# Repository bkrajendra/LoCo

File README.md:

# LoCo - A LoRa-concentrator

An Opensource LoRa Concentrator/Gateway using SX1301/SX1308 and SX1255/SX1257 For RRI and RPI Zero.

This project is heavyly inspired and adapted from @will127534 works he has done for his contribution at https://github.com/will127534/LoRa-concentrator.

We just want to take this project ahead and updating it with most commonly avialibility of componenets.

The first step is to port the schematic to KiCad to make the process of devlopment easier as an opensource project.

<!-- Copy-paste in your Readme.md file -->
## Contributors

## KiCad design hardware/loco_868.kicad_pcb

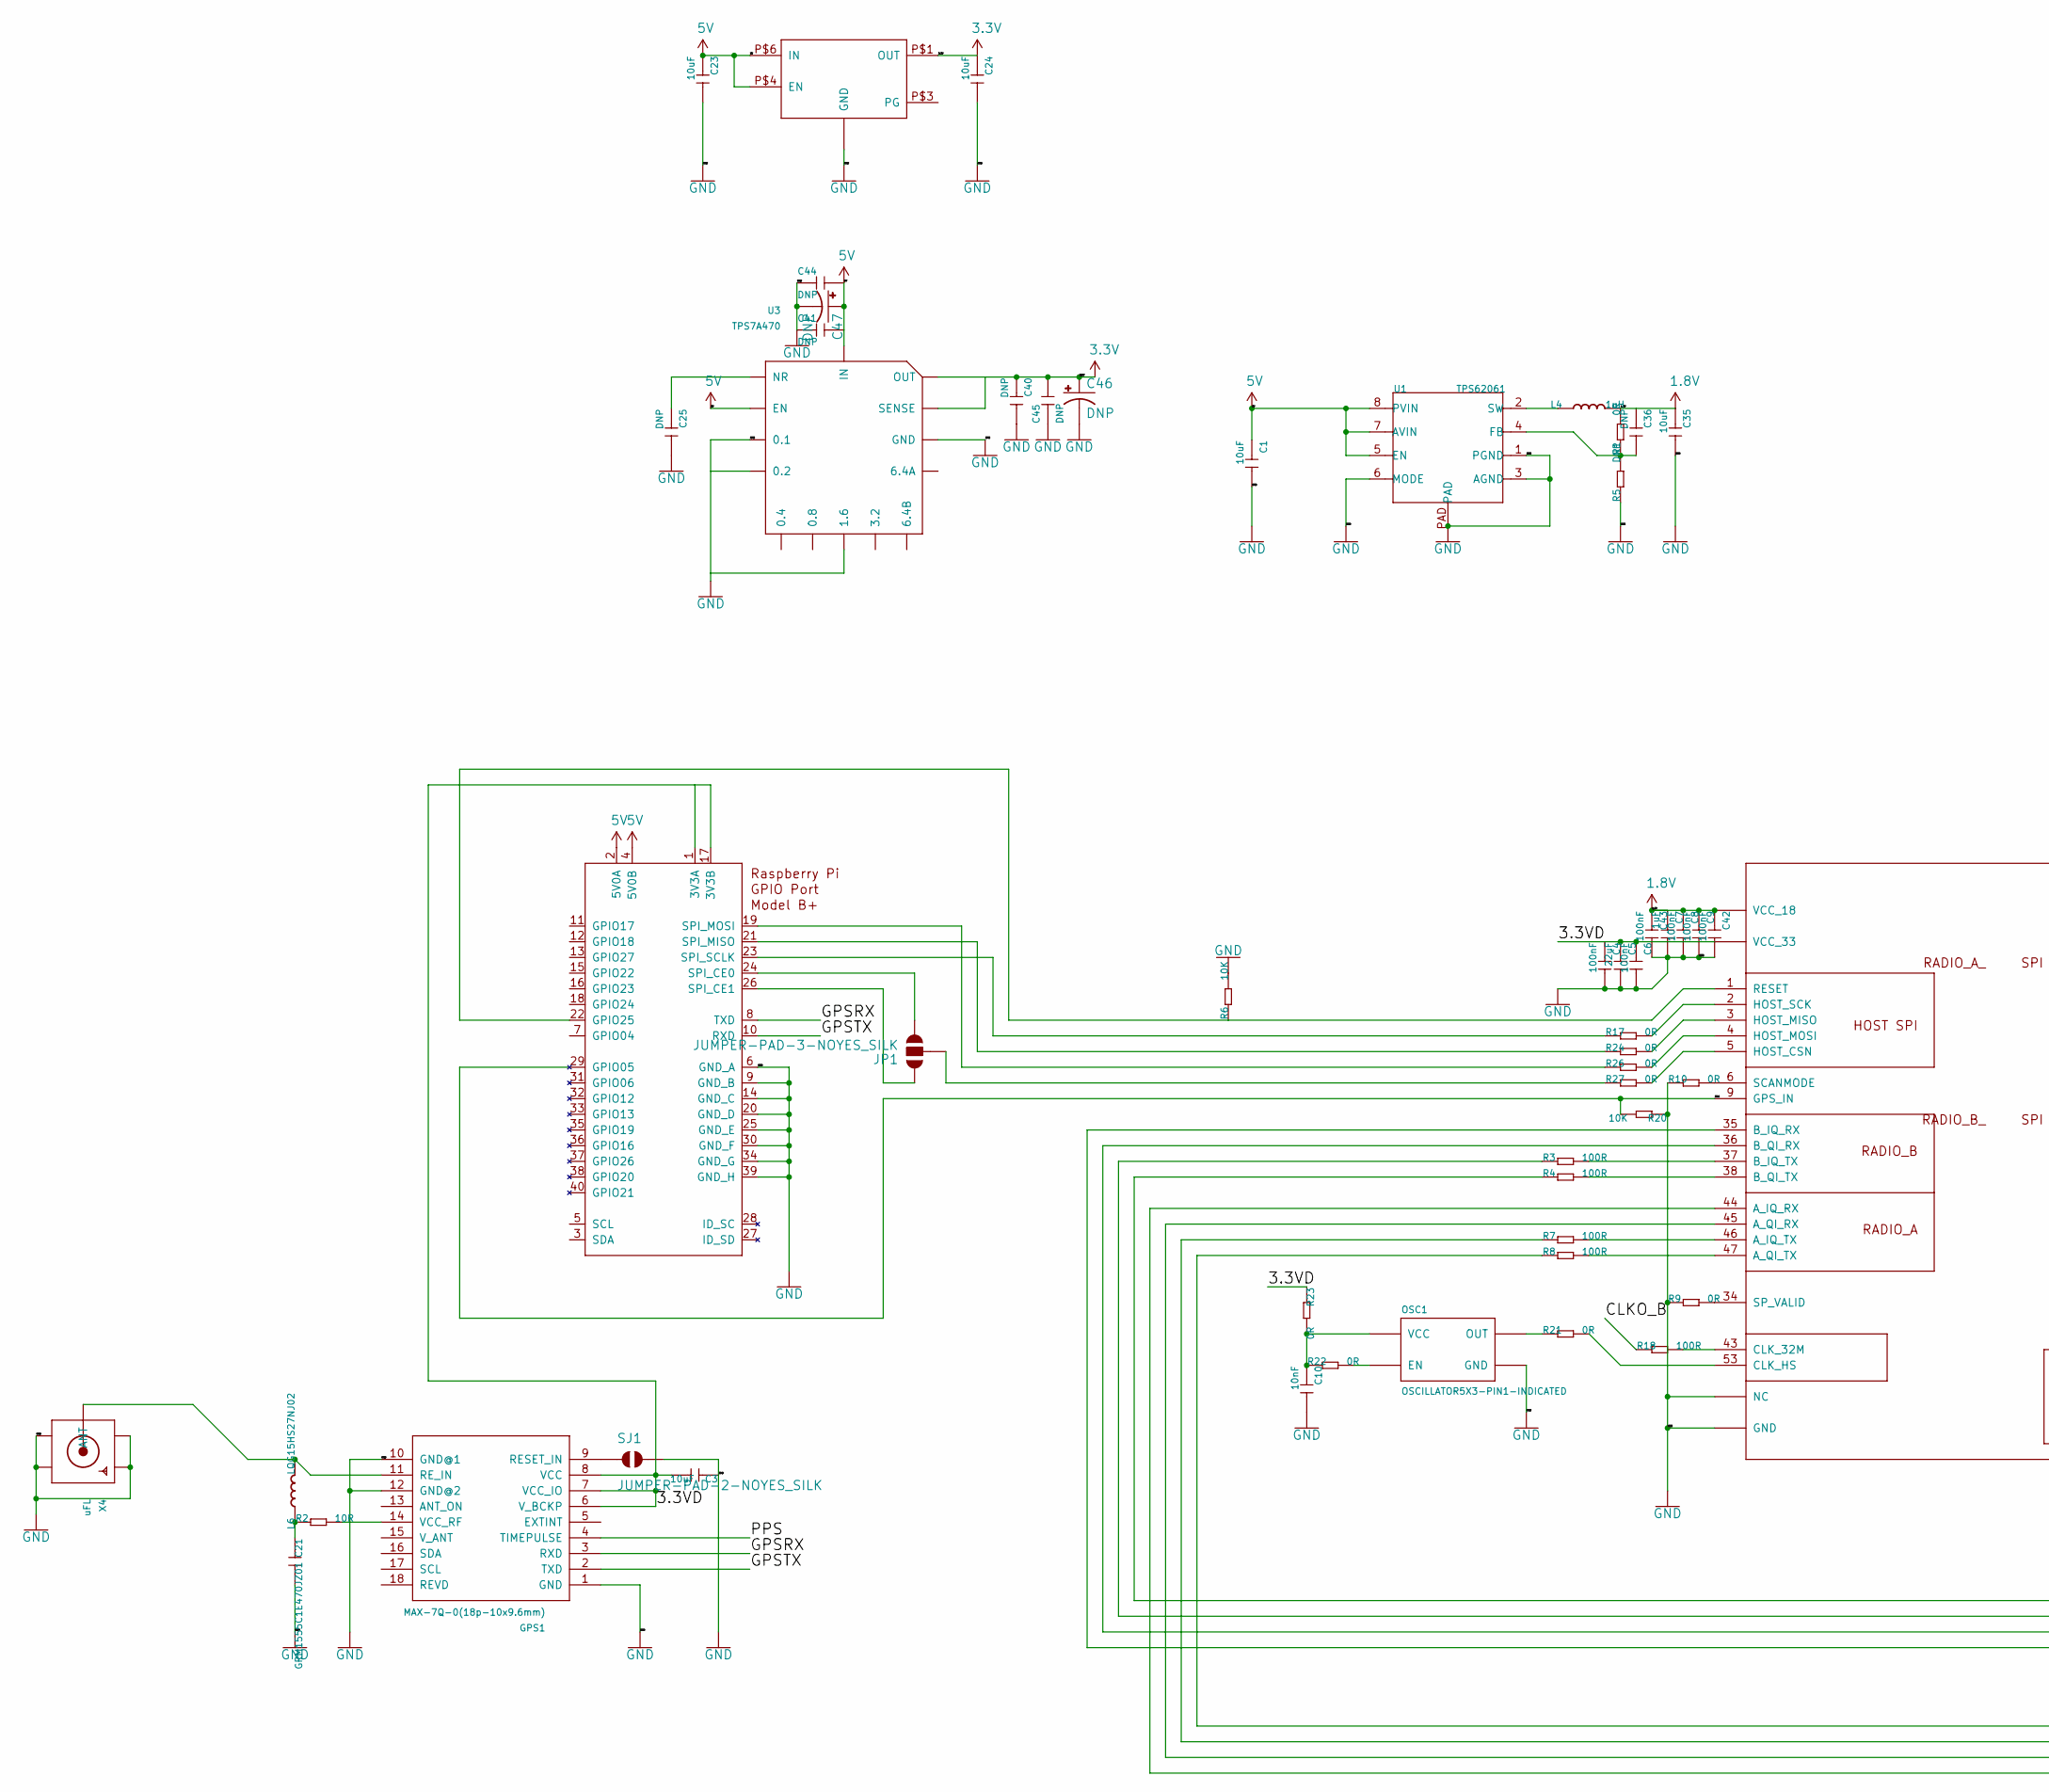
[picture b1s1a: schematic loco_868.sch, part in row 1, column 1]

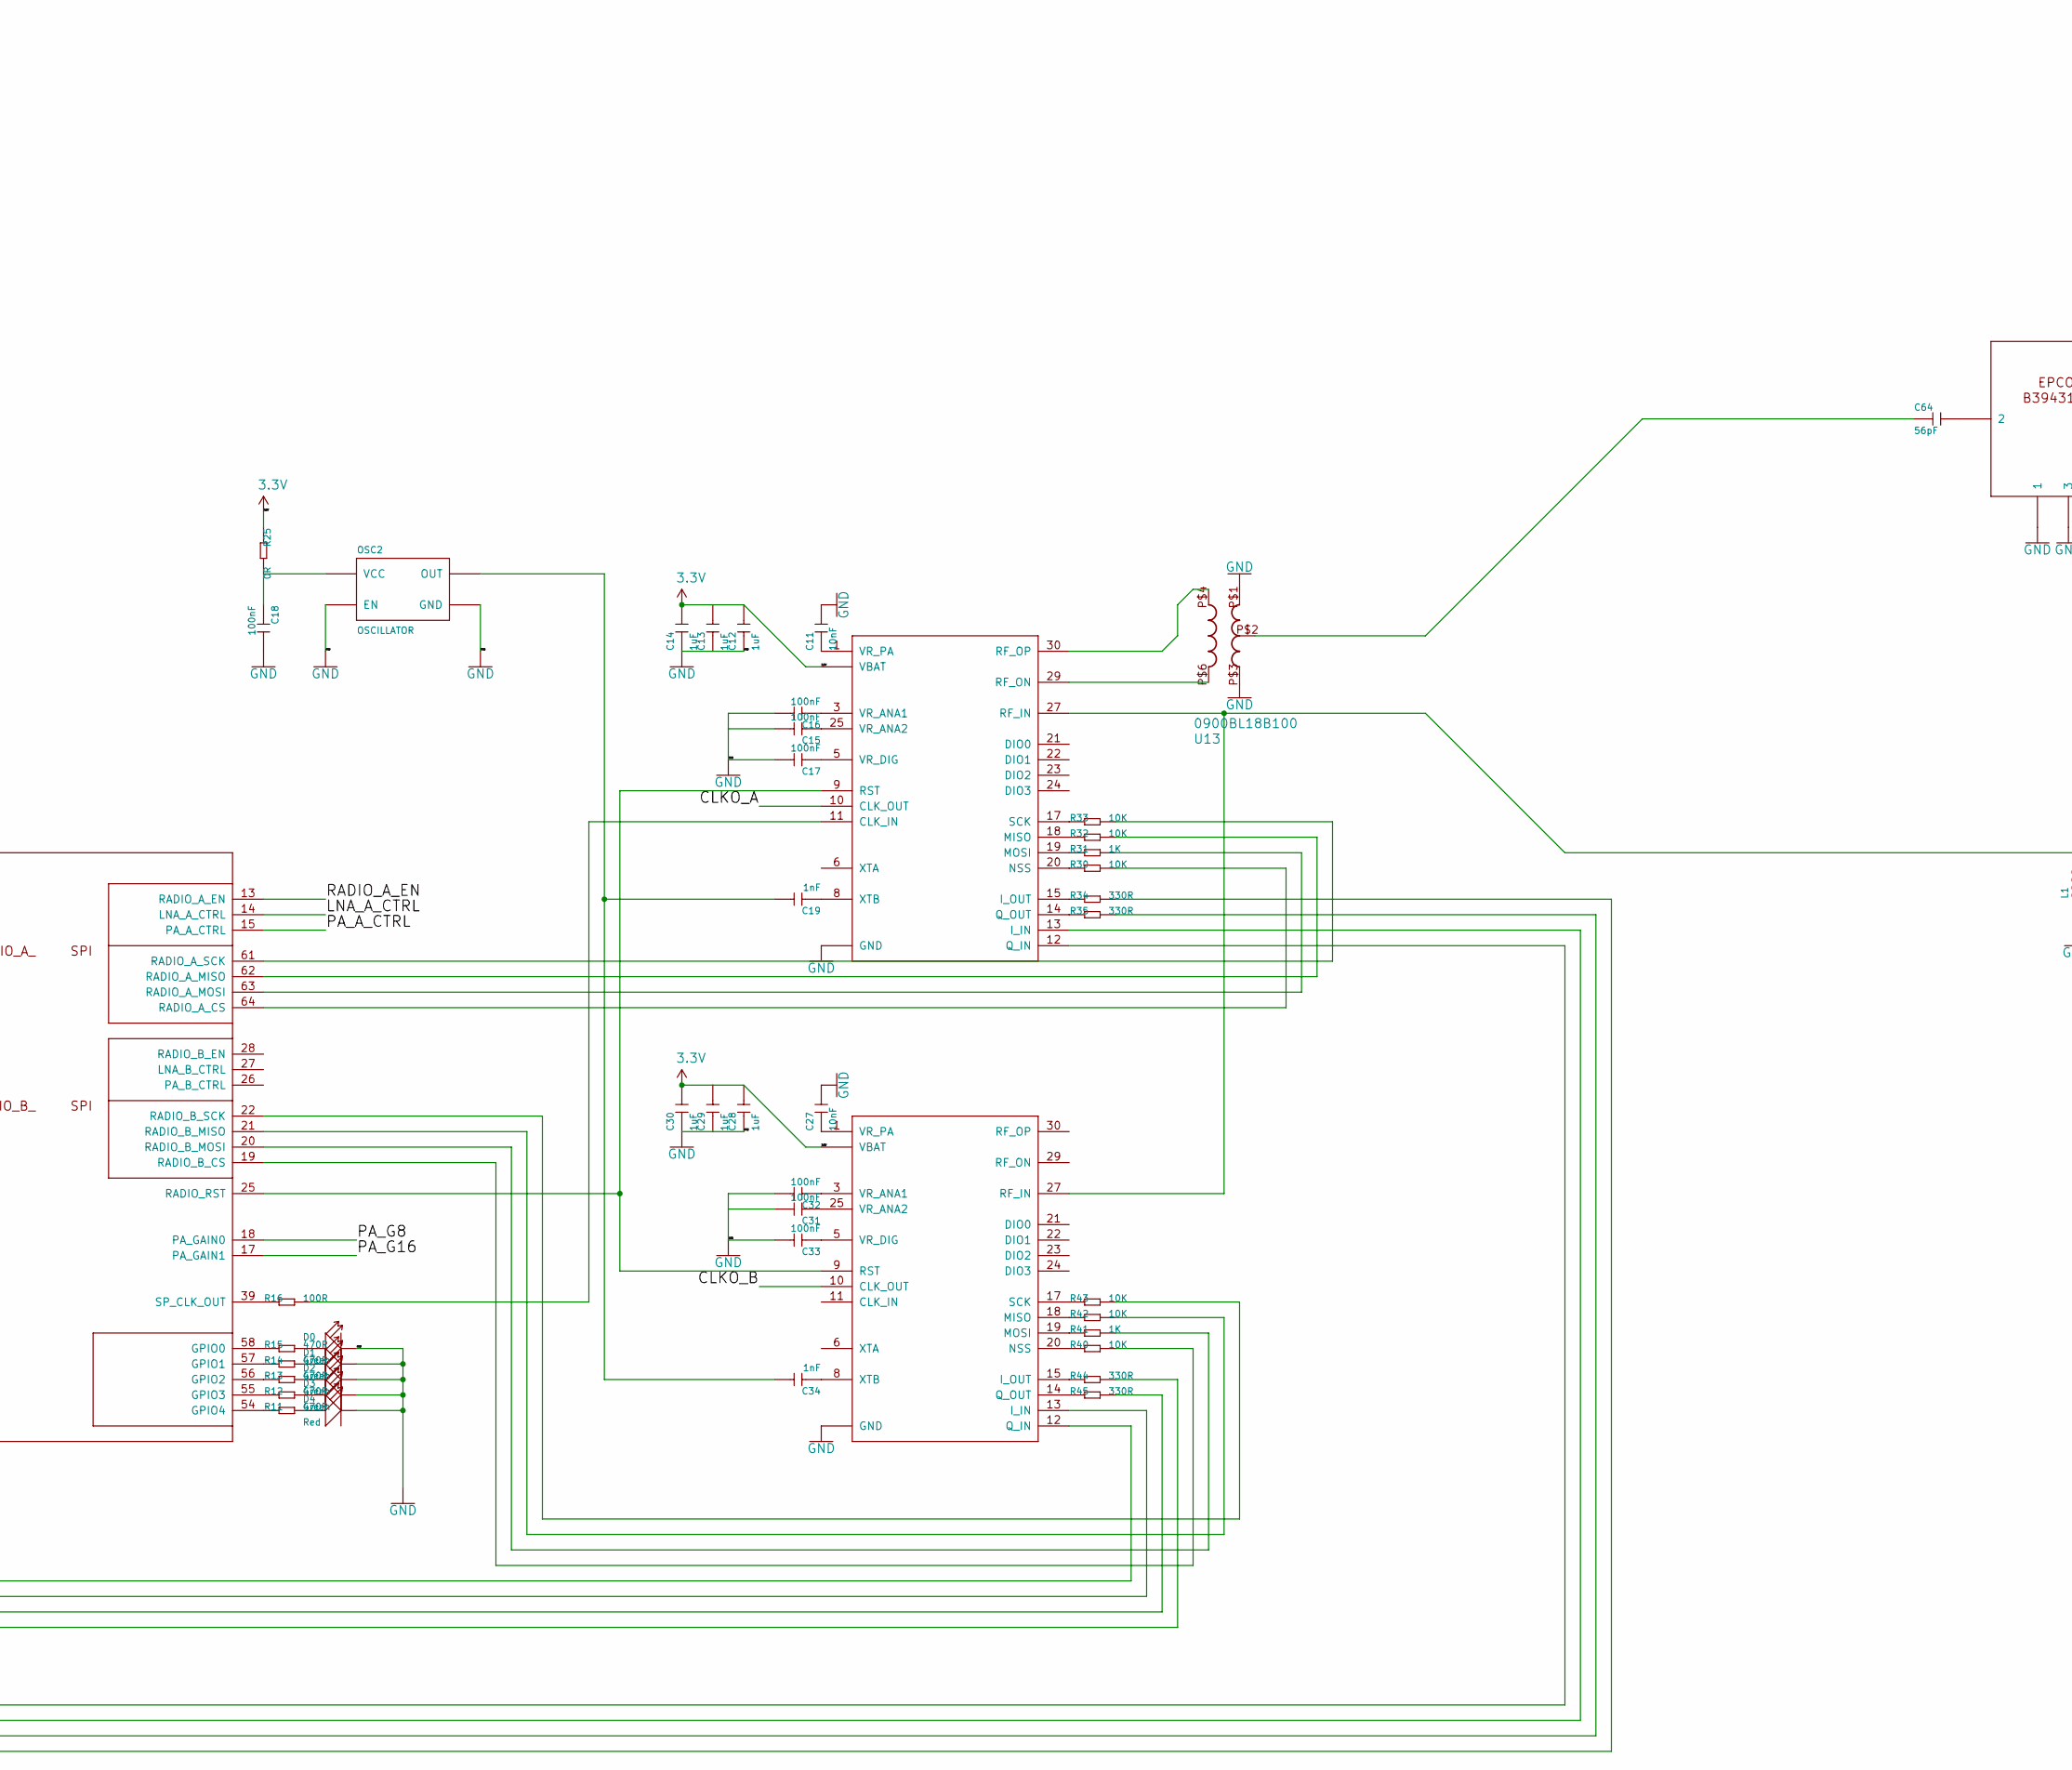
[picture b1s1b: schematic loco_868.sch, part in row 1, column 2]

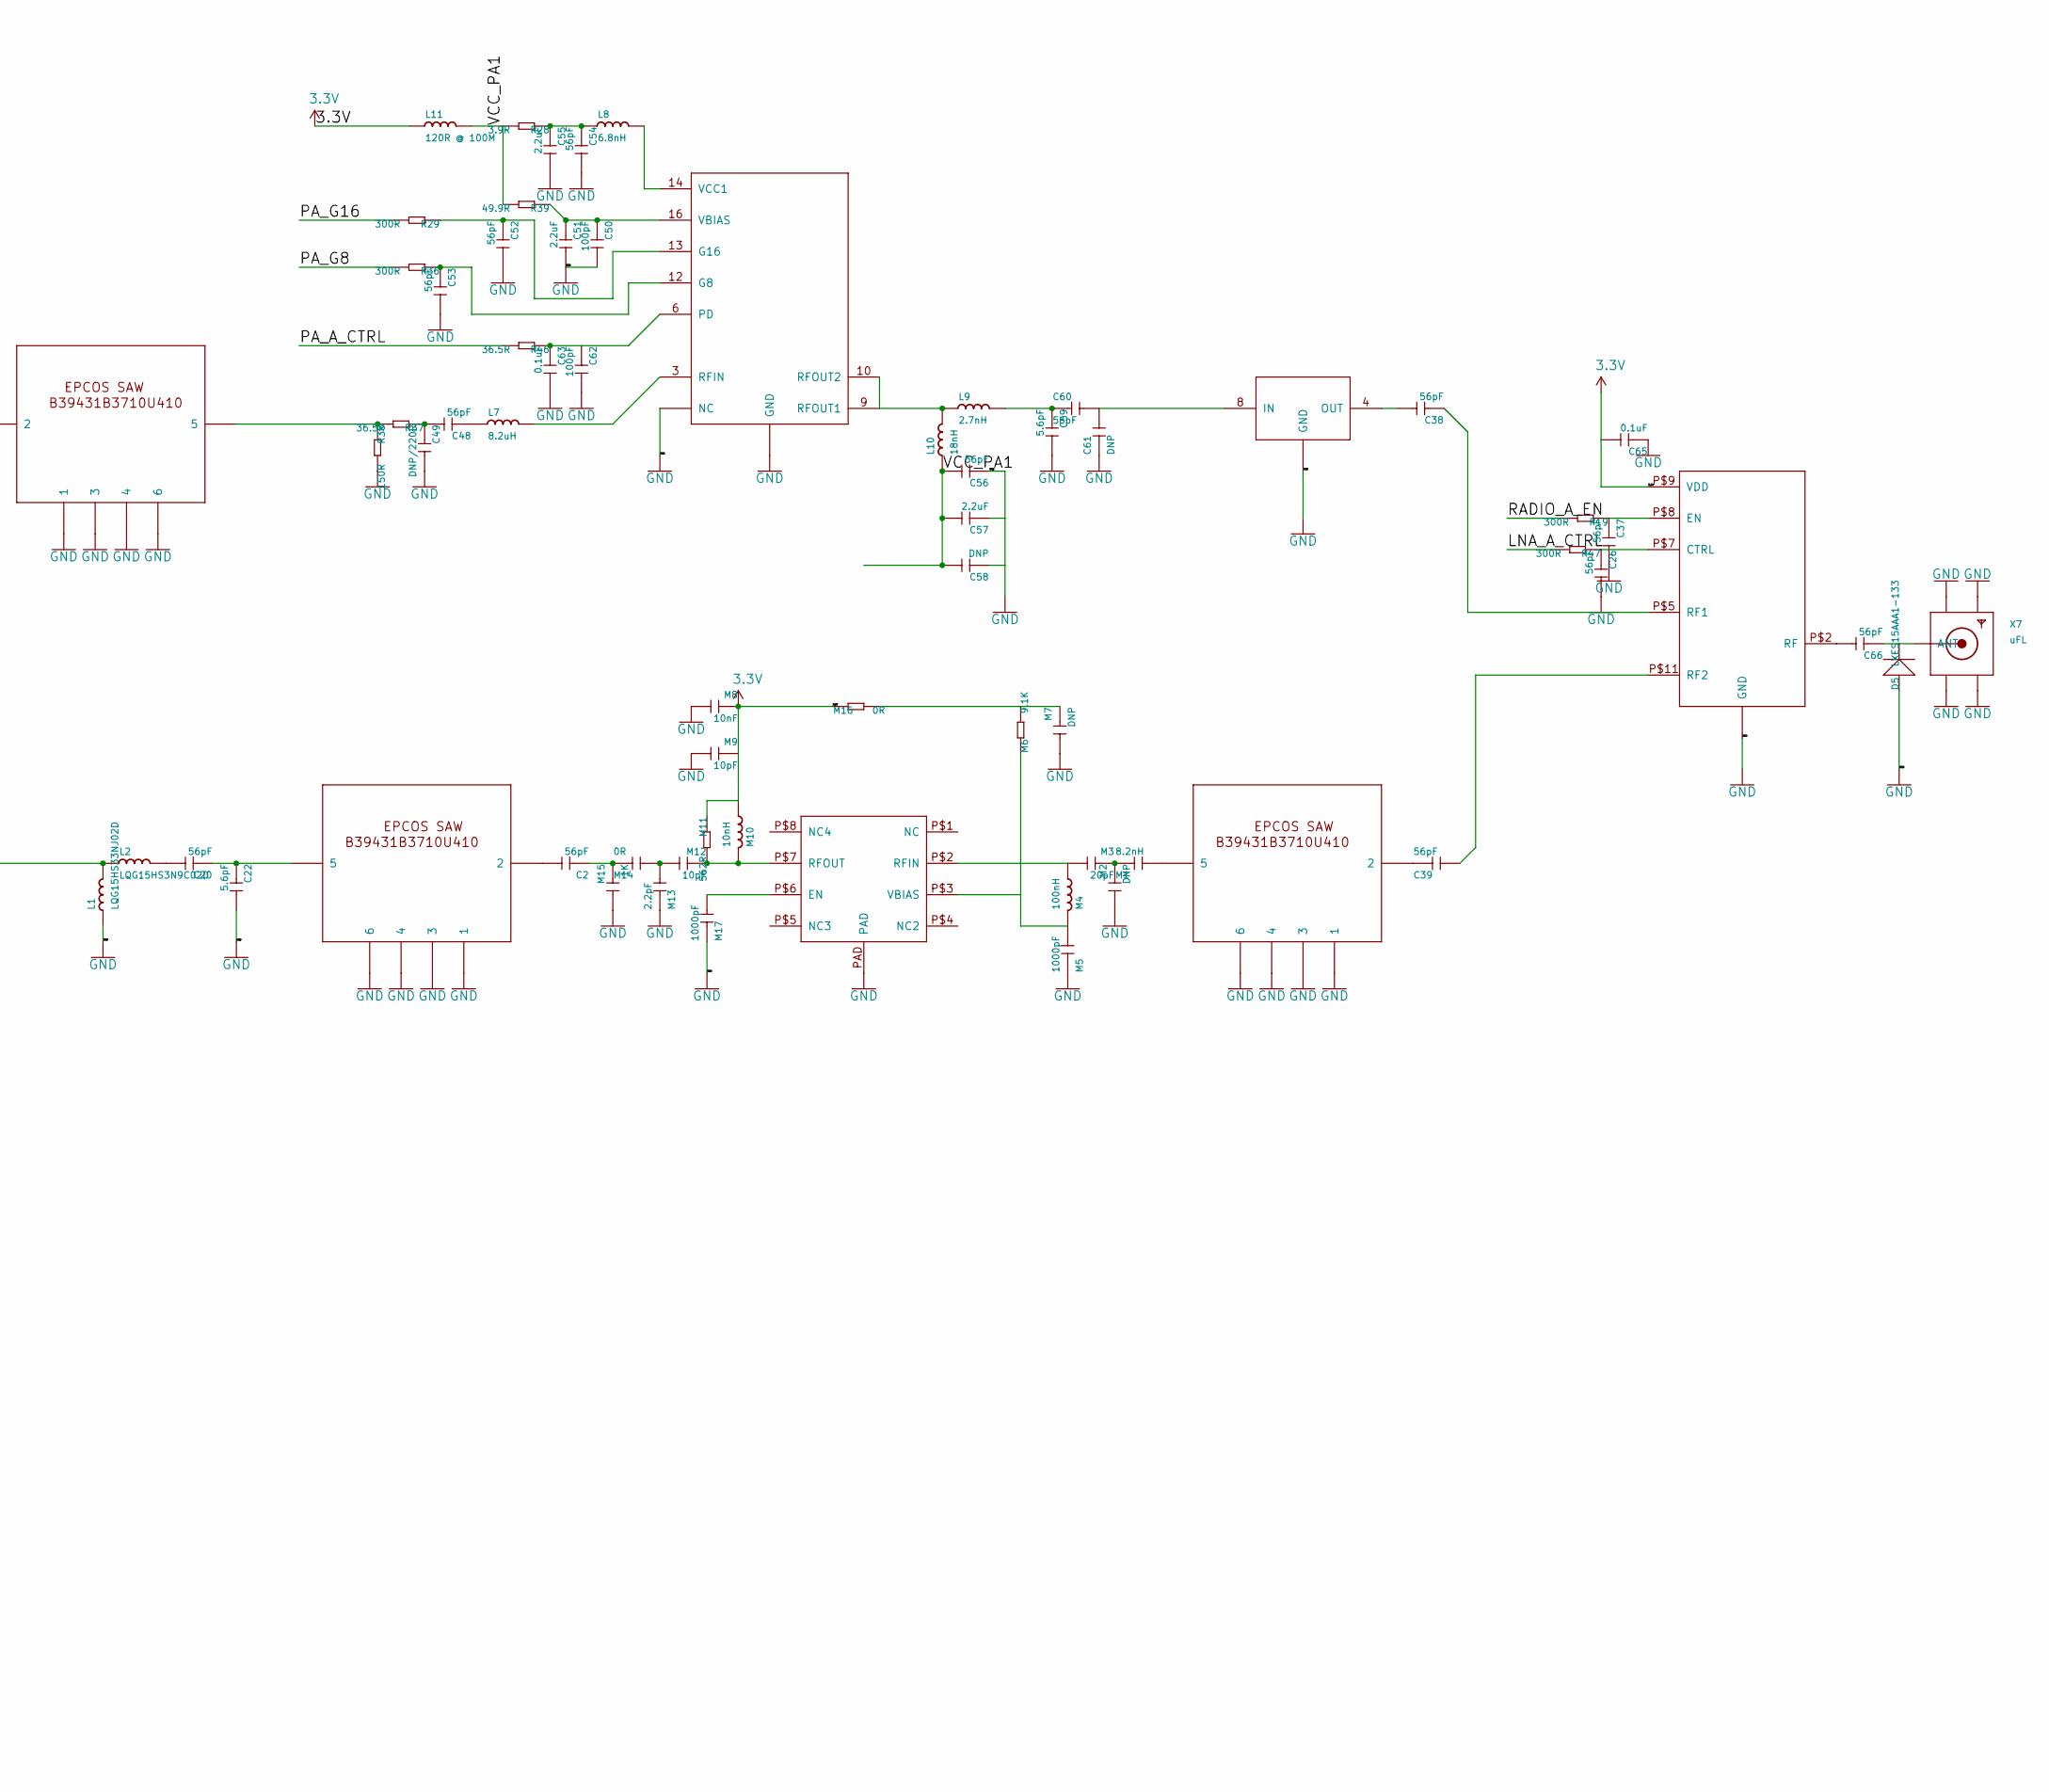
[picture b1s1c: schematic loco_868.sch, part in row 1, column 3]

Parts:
C1, C23, C24, C35: 10uF; C0603@1
C2, C20, C26, C37, C38, C39, C48, C52, C53, C54, C56, C60, C64, C66: 56pF; C0402@1
C3: 10uF; C0603
C4, C6, C8, C9, C15, C16, C17, C18, C31, C32, C33, C42, C43: 100nF; C0402@1
C5: 22uF; C0402@1
C7, C12, C13, C14, C28, C29, C30: 1uF; C0402@1
C10, C11, C27: 10nF; C0402@1
C19, C34: 1nF; C0402@1
C21: GRM1555C1E470JZ01; C0402
C22, C59: 5.6pF; C0402@1
C25, C36, C40, C41, C58, C61: DNP; C0402@1
C44, C45: DNP; C0805@1
C46, C47: DNP; EIA3216
C49: DNP/220R; C0402@1
C50, C62: 100pF; C0402@1
C51, C55, C57: 2.2uF; C0402@1
C63, C65: 0.1uF; C0402@1
D0, D1, D2, D3: Green; LED-0603
D4: Red; LED-0603
D5: LXES15AAA1-133; C0402
GPS1: MAX-7Q-0(18p-10x9.6mm); GPS18P-SMD-1.1-10X9.6MM
JP1: JUMPER-PAD-3-NOYES_SILK; PAD-JUMPER-3-NO_YES_SILK
L1: LQG15HS33NJ02D; L0402@1
L2: LQG15HS3N9C02D; L0402@1
L4: 1uH; 1616BZ
L6: LQG15HS27NJ02; L0402
L7: 8.2uH; L0402@1
L8: 6.8nH; L0402@1
L9: 2.7nH; L0402@1
L10: 18nH; L0402@1
L11: 120R @ 100M; L0402@1
M1: 8.2nH; C0402@1
M2, M7: DNP; C0402@1
M3: 20pF; C0402@1
M4: 100nH; L0402@1
M5, M17: 1000pF; C0402@1
M6: 9.1K; R0402
M8: 10nF; C0402@1
M9, M12: 10pF; C0402@1
M10: 10nH; L0402@1
M11: 562R; R0402
M13: 2.2pF; C0402@1
M14: 0R; C0402@1
M15: 1K; C0402@1
M16: 0R; R0402
OSC1: OSCILLATOR5X3-PIN1-INDICATED; CRYSTAL-OSC-SMD-5X3
OSC2: OSCILLATOR; CRYSTAL-OSC-SMD-3.2X2.5
R1, R9, R10, R17, R21, R22, R23, R24, R25, R26, R27: 0R; R0402
R2: 10R; R0402
R3, R4, R7, R8, R16, R18: 100R; R0402
R5: DNP; R0402
R6, R20, R30, R32, R33, R40, R42, R43: 10K; R0402
R11, R12, R13, R14, R15: 470R; R0402
R19, R29, R36, R47: 300R; R0402
R28: 3.9R; R0402
R31, R41: 1K; R0402
R34, R35, R44, R45: 330R; R0402
R37, R46: 36.5R; R0402
R38: 150R; R0402
R39: 49.9R; R0402
SJ1: JUMPER-PAD-2-NOYES_SILK; PAD-JUMPER-2-NO_YES_SILK
U1: TPS62061; WSON
U3: TPS7A470; S-PVQFN-N20
U6: RFPA0133; QFN16-3X3MM
U13: 0900BL18B100; BALUN_1206
U$1: SX1301; QFN64G-0.5-9X9MM
U$2, U$3: SX1255; QFN32G-0.5-5X5MM
U$4, U$8: B39921B3728U410; EPCOS_SAW_FILTER
U$5: LP5912; WSON6
U$6: 0915LP15B026
U$7: RFSW1012; QFN12-2X2MM
U$9: EPCOS_SAW_FILTER
U$10: SKY67150_396LF; 8DFN
X1: RASPI_BOARD_B+#_H; RASPI_BOARD_B+HAT
X4, X7: uFL; SMA_EDGELAUNCH_UFL

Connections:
1.8V: C7.1, C8.1, C9.1, C35.1, C36.1, C42.1, C43.1, L4.2, R1.2, U$1.8 (VCC_18), U$1.12 (VCC_18), U$1.23 (VCC_18), U$1.42 (VCC_18), U$1.60 (VCC_18)
3.3V: C12.2, C13.2, C14.2, C24.1, C28.2, C29.2, C30.2, C40.1, C45.2, C46.A (+), C65.2, L11.1, M8.1, M9.1, M10.2, M11.1, M16.1, R25.1, U3.1 (OUT), U3.3 (SENSE), U3.20 (OUT), U$2.2 (VBAT), U$2.16 (VBAT), U$2.32 (VBAT), U$3.2 (VBAT), U$3.16 (VBAT), U$3.32 (VBAT), U$5.P$1 (OUT), U$7.P$9 (VDD)
5V: C1.1, C23.1, C41.2, C44.2, C47.A (+), U1.5 (EN), U1.7 (AVIN), U1.8 (PVIN), U3.13 (EN), U3.15 (IN), U3.16 (IN), U$5.P$4 (EN), U$5.P$6 (IN), X1.2 (5V0A), X1.4 (5V0B)
/3.3VD: C3.2, C4.1, C5.1, C6.1, GPS1.6 (V_BCKP), GPS1.7 (VCC_IO), GPS1.8 (VCC), R23.1, U$1.29 (VCC_33), U$1.52 (VCC_33), X1.1 (3V3A), X1.17 (3V3B)
/CLKO_A: U$2.10 (CLK_OUT)
/CLKO_B: R18.1, U$3.10 (CLK_OUT)
/GPSRX: GPS1.3 (RXD), X1.8 (TXD)
/GPSTX: GPS1.2 (TXD), X1.10 (RXD)
/LNA_A_CTRL: R47.2, U$1.14 (LNA_A_CTRL)
/PA_A_CTRL: R46.2, U$1.15 (PA_A_CTRL)
/PA_G8: R36.2, U$1.18 (PA_GAIN0)
/PA_G16: R29.2, U$1.17 (PA_GAIN1)
/PPS: GPS1.4 (TIMEPULSE), R20.2, U$1.9 (GPS_IN), X1.29 (GPIO05)
/RADIO_A_EN: R19.2, U$1.13 (RADIO_A_EN)
/VCC_PA1: C56.2, C57.2, C58.2, L10.1, L11.2, R28.2, R39.2
GND: C1.2, C3.1, C4.2, C5.2, C6.2, C7.2, C8.2, C9.2, C10.2, C11.2, C12.1, C13.1, C14.1, C15.2, C16.2, C17.2, C18.2, C21.2, C22.2, C23.2, C24.2, C25.2, C26.2, C27.2, C28.1, C29.1, C30.1, C31.2, C32.2, C33.2, C35.2, C37.2, C40.2, C41.1, C42.2, C43.2, C44.1, C45.1, C46.C (-), C47.C (-), C49.2, C50.2, C51.2, C52.2, C53.2, C54.2, C55.2, C56.1, C57.1, C58.1, C59.2, C61.1, C62.2, C63.2, C65.1, D0.-, D1.-, D2.-, D3.-, D4.-, D5.1 (+), GPS1.1 (GND), GPS1.10 (GND@1), GPS1.12 (GND@2), L1.1, M2.2, M5.1, M7.2, M8.2, M9.2, M13.1, M15.2, M17.1, OSC1.2 (GND), OSC2.P$1 (EN), OSC2.P$2 (GND), R5.1, R6.2, R9.1, R10.1, R20.1, R38.2, SJ1.2, U1.1 (PGND), U1.3 (AGND), U1.6 (MODE), U1.PAD, U3.2 (GND), U3.7 (GND), U3.8 (1.6), U3.11 (0.2), U3.12 (0.1), U3.17 (GND), U3.18 (GND), U3.19 (GND), U3.EXP (GND), U6.1 (NC), U6.2 (GND), U6.4 (NC), U6.5 (NC), U6.7 (NC), U6.8 (NC), U6.11 (NC), U6.15 (NC), U6.EXT (GND), U13.P$1 (GND_1), U13.P$3 (GND_2), U$1.7 (GND), U$1.10 (GND), U$1.11 (GND), U$1.16 (NC), U$1.24 (GND), U$1.30 (GND), U$1.31 (GND), U$1.32 (NC), U$1.33 (NC), U$1.40 (GND), U$1.41 (GND), U$1.48 (NC), U$1.49 (NC), U$1.50 (GND), U$1.51 (GND), U$1.59 (GND), U$1.65 (GND), U$2.4 (GND), U$2.7 (GND), U$2.26 (GND), U$2.28 (GND), U$2.31 (GND), U$2.33 (GND), U$3.4 (GND), U$3.7 (GND), U$3.26 (GND), U$3.28 (GND), U$3.31 (GND), U$3.33 (GND), U$4.P$1 (1), U$4.P$3 (3), U$4.P$4 (4), U$4.P$6 (6), U$5.P$2 (GND), U$5.P$5 (GND), U$5.PAD (GND), U$6.1 (GND), U$6.3 (GND), U$6.5 (GND), U$6.7 (GND), U$7.P$1 (GND), U$7.P$3 (GND), U$7.P$4 (GND), U$7.P$6 (GND), U$7.P$10 (GND), U$7.P$12 (GND), U$7.PAD (GND), U$8.P$1 (1), U$8.P$3 (3), U$8.P$4 (4), U$8.P$6 (6), U$9.P$1 (1), U$9.P$3 (3), U$9.P$4 (4), U$9.P$6 (6), U$10.PAD, X1.6 (GND_A), X1.9 (GND_B), X1.14 (GND_C), X1.20 (GND_D), X1.25 (GND_E), X1.30 (GND_F), X1.34 (GND_G), X1.39 (GND_H), X4.GND@1 (GND1), X4.GND@2 (GND2), X4.GND@3 (GND3), X4.GND@4 (GND4), X7.GND@1 (GND1), X7.GND@2 (GND2), X7.GND@3 (GND3), X7.GND@4 (GND4)
unnamed: C2.1, M14.1, M15.1
unnamed: C2.2, U$4.P$2 (2)
unnamed: C10.1, OSC1.4 (VCC), R22.1, R23.2
unnamed: C11.1, U$2.1 (VR_PA)
unnamed: C15.1, U$2.25 (VR_ANA2)
unnamed: C16.1, U$2.3 (VR_ANA1)
unnamed: C17.1, U$2.5 (VR_DIG)
unnamed: C18.1, OSC2.P$4 (VCC), R25.2
unnamed: C19.1, U$2.8 (XTB)
unnamed: C19.2, C34.2, OSC2.P$3 (OUT)
unnamed: C20.1, C22.1, U$4.P$5 (5)
unnamed: C20.2, L2.2
unnamed: C21.1, L6.1, R2.1
unnamed: C25.1, U3.14 (NR)
unnamed: C26.1, R47.1, U$7.P$7 (CTRL)
unnamed: C27.1, U$3.1 (VR_PA)
unnamed: C31.1, U$3.25 (VR_ANA2)
unnamed: C32.1, U$3.3 (VR_ANA1)
unnamed: C33.1, U$3.5 (VR_DIG)
unnamed: C34.1, U$3.8 (XTB)
unnamed: C36.2, R1.1, R5.2, U1.4 (FB)
unnamed: C37.1, R19.1, U$7.P$8 (EN)
unnamed: C38.1, U$7.P$5 (RF1)
unnamed: C38.2, U$6.4 (OUT)
unnamed: C39.1, U$9.P$2 (2)
unnamed: C39.2, U$7.P$11 (RF2)
unnamed: C48.1, L7.1
unnamed: C48.2, C49.1, R37.1
unnamed: C50.1, C51.1, R39.1, U6.16 (VBIAS)
unnamed: C52.1, R29.1, U6.13 (G16)
unnamed: C53.1, R36.1, U6.12 (G8)
unnamed: C54.1, C55.1, L8.1, R28.1
unnamed: C59.1, C60.1, L9.2
unnamed: C60.2, C61.2, U$6.8 (IN)
unnamed: C62.1, C63.1, R46.1, U6.6 (PD)
unnamed: C64.1, U13.P$2 (UNBALANCE)
unnamed: C64.2, U$8.P$2 (2)
unnamed: C66.1, D5.2 (-), X7.P (ANT)
unnamed: C66.2, U$7.P$2 (RF)
unnamed: D0.+, R15.2
unnamed: D1.+, R14.2
unnamed: D2.+, R13.2
unnamed: D3.+, R12.2
unnamed: D4.+, R11.2
unnamed: GPS1.9 (RESET_IN), SJ1.1
unnamed: GPS1.11 (RE_IN), L6.2, X4.P (ANT)
unnamed: GPS1.14 (VCC_RF), R2.2
unnamed: JP1.1, X1.26 (SPI_CE1)
unnamed: JP1.2, R27.1
unnamed: JP1.3, X1.24 (SPI_CE0)
unnamed: L1.2, L2.1, U$2.27 (RF_IN), U$3.27 (RF_IN)
unnamed: L4.1, U1.2 (SW)
unnamed: L7.2, U6.3 (RFIN)
unnamed: L8.2, U6.14 (VCC1)
unnamed: L9.1, L10.2, U6.9 (RFOUT1), U6.10 (RFOUT2)
unnamed: M1.1, M2.1, M3.1
unnamed: M1.2, U$9.P$5 (5)
unnamed: M3.2, M4.2, U$10.P$2 (RFIN)
unnamed: M4.1, M5.2, M6.1, U$10.P$3 (VBIAS)
unnamed: M10.1, M11.2, M12.1, U$10.P$7 (RFOUT)
unnamed: M12.2, M13.2, M14.2
unnamed: M6.2, M7.1, M16.2
unnamed: M17.2, U$10.P$6 (EN)
unnamed: OSC1.1 (EN), R22.2
unnamed: OSC1.3 (OUT), R21.1
unnamed: R3.1, U$3.13 (I_IN)
unnamed: R3.2, U$1.37 (B_IQ_TX)
unnamed: R4.1, U$3.12 (Q_IN)
unnamed: R4.2, U$1.38 (B_QI_TX)
unnamed: R6.1, U$1.1 (RESET), X1.22 (GPIO25)
unnamed: R7.1, U$2.13 (I_IN)
unnamed: R7.2, U$1.46 (A_IQ_TX)
unnamed: R8.1, U$2.12 (Q_IN)
unnamed: R8.2, U$1.47 (A_QI_TX)
unnamed: R9.2, U$1.34 (SP_VALID)
unnamed: R10.2, U$1.6 (SCANMODE)
unnamed: R11.1, U$1.54 (GPIO4)
unnamed: R12.1, U$1.55 (GPIO3)
unnamed: R13.1, U$1.56 (GPIO2)
unnamed: R14.1, U$1.57 (GPIO1)
unnamed: R15.1, U$1.58 (GPIO0)
unnamed: R16.1, U$1.39 (SP_CLK_OUT)
unnamed: R16.2, U$2.11 (CLK_IN)
unnamed: R17.1, X1.23 (SPI_SCLK)
unnamed: R17.2, U$1.2 (HOST_SCK)
unnamed: R18.2, U$1.43 (CLK_32M)
unnamed: R21.2, U$1.53 (CLK_HS)
unnamed: R24.1, X1.21 (SPI_MISO)
unnamed: R24.2, U$1.3 (HOST_MISO)
unnamed: R26.1, X1.19 (SPI_MOSI)
unnamed: R26.2, U$1.4 (HOST_MOSI)
unnamed: R27.2, U$1.5 (HOST_CSN)
unnamed: R30.1, U$2.20 (NSS)
unnamed: R30.2, U$1.64 (RADIO_A_CS)
unnamed: R31.1, U$2.19 (MOSI)
unnamed: R31.2, U$1.63 (RADIO_A_MOSI)
unnamed: R32.1, U$2.18 (MISO)
unnamed: R32.2, U$1.62 (RADIO_A_MISO)
unnamed: R33.1, U$2.17 (SCK)
unnamed: R33.2, U$1.61 (RADIO_A_SCK)
unnamed: R34.1, U$2.15 (I_OUT)
unnamed: R34.2, U$1.44 (A_IQ_RX)
unnamed: R35.1, U$2.14 (Q_OUT)
unnamed: R35.2, U$1.45 (A_QI_RX)
unnamed: R37.2, R38.1, U$8.P$5 (5)
unnamed: R40.1, U$3.20 (NSS)
unnamed: R40.2, U$1.19 (RADIO_B_CS)
unnamed: R41.1, U$3.19 (MOSI)
unnamed: R41.2, U$1.20 (RADIO_B_MOSI)
unnamed: R42.1, U$3.18 (MISO)
unnamed: R42.2, U$1.21 (RADIO_B_MISO)
unnamed: R43.1, U$3.17 (SCK)
unnamed: R43.2, U$1.22 (RADIO_B_SCK)
unnamed: R44.1, U$3.15 (I_OUT)
unnamed: R44.2, U$1.35 (B_IQ_RX)
unnamed: R45.1, U$3.14 (Q_OUT)
unnamed: R45.2, U$1.36 (B_QI_RX)
unnamed: U$1.25 (RADIO_RST), U$2.9 (RST), U$3.9 (RST)
unnamed: U13.P$6 (BALANCE_2), U$2.29 (RF_ON)
unnamed: U13.P$4 (BALANCE_1), U$2.30 (RF_OP)

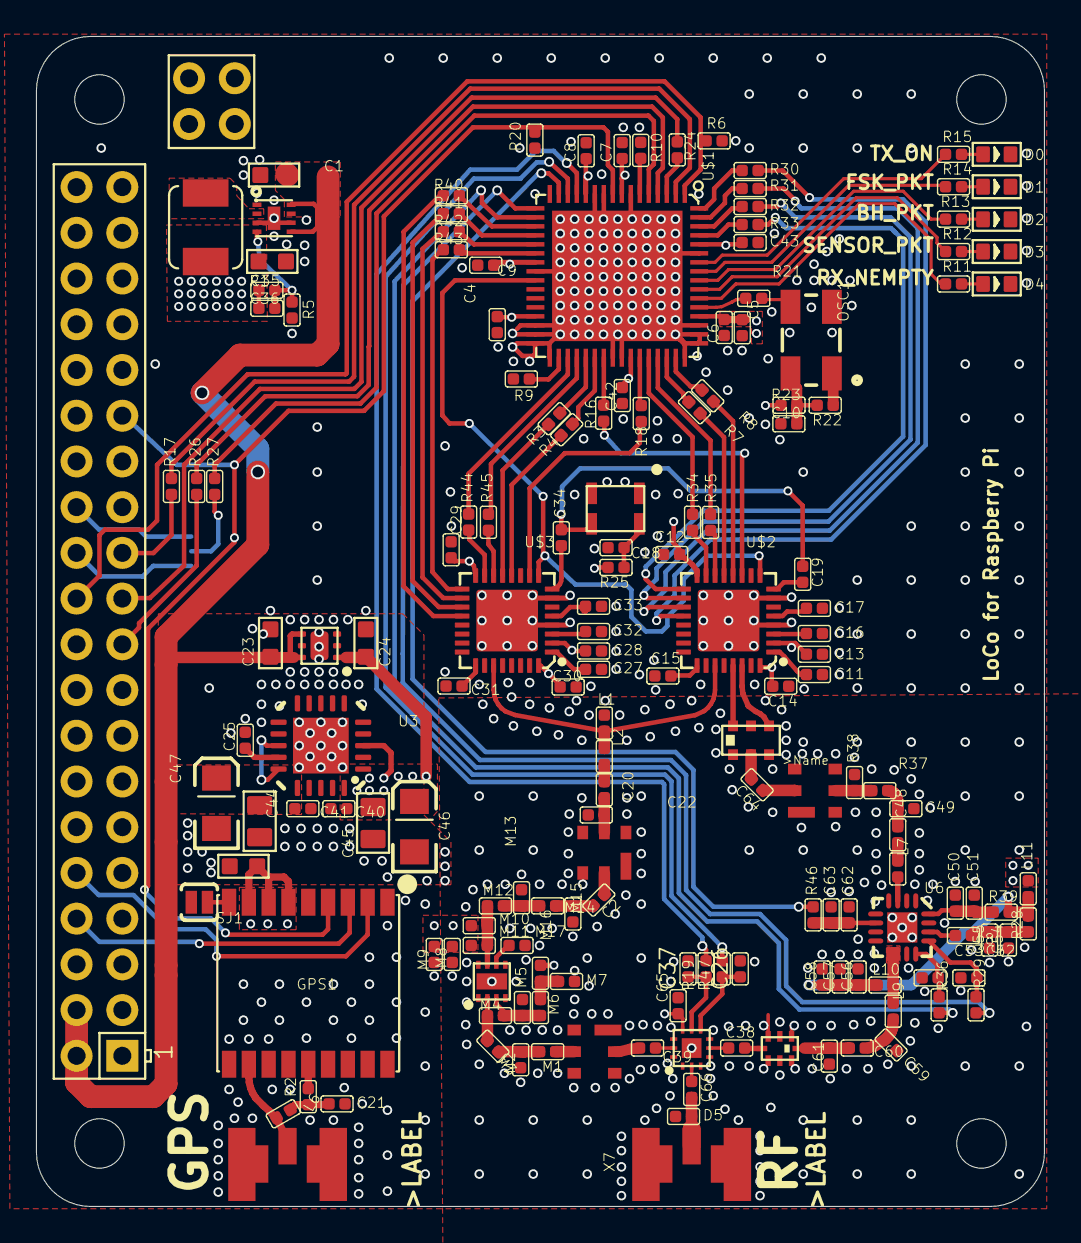
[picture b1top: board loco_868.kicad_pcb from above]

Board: 16 copper layers, 56.0 x 65.0 mm, 167 parts (0 on the bottom side), 135 nets.

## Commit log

2021-08-22 readme update
2021-08-22 update contri
2021-08-22 basic porting of schematic to KiCad
2021-08-22 test render
